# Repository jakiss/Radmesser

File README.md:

# Radmesser
For the enlish version see below.

Das Projekt befasst sich mit der Entwicklung eines Radmessers nach der Idee des Tagesspiegel Berlin (Vgl. https://interaktiv.tagesspiegel.de/radmesser/ und https://github.com/tagesspiegel/radmesser). 

Die genaue des Beschreibung des Projekts mit Grundidee und Annahmen findet sich unter Projektbeschreibung.pdf, um eine kurze Zusammenfassung zu erhalten empfiehlt sich die Datei Zusammenfassung_Projektbeschreibung.pdf.

------------------------------------------------------------
English version:

The project deals with the development of a measurement system for the overtaking distance between cars and bicycles after the idea of the Tagesspeigel Berlin (see https://interaktiv.tagesspiegel.de/radmesser/ and https://github.com/tagesspiegel/radmesser).

The detailed description of the project including the main idea and assumptions  can be found in Projektbeschreibung.pdf. For a short summary of the topic the file Zusammenfassung_Projektbeschreibung.pdf is recommended.

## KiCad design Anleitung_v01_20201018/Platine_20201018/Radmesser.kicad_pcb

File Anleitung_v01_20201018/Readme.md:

Die ausführliche Anleitung finden Sie in der Datei Anleitung.pdf.
Wir haben derzeit noch ein kleines Problem mit unserem Temperatursensor auf der Softwareseite, werden jedoch versuchen dieses so schnell wie möglich zu beheben und ein aktualisiertes Image zur Verfügung zu stellen.

Für den späteren Betrieb ist es wichtig, dass nach einem anfänglichen Blincken im Gleichtakt der LEDs nur noch die grüne LED leuchtet.
Ist dies nicht der Fall, liegt ein Fehler vor. Die rote LED blinkt immer dann auf, wenn ein falscher Messwert aufgezeichent wurde.

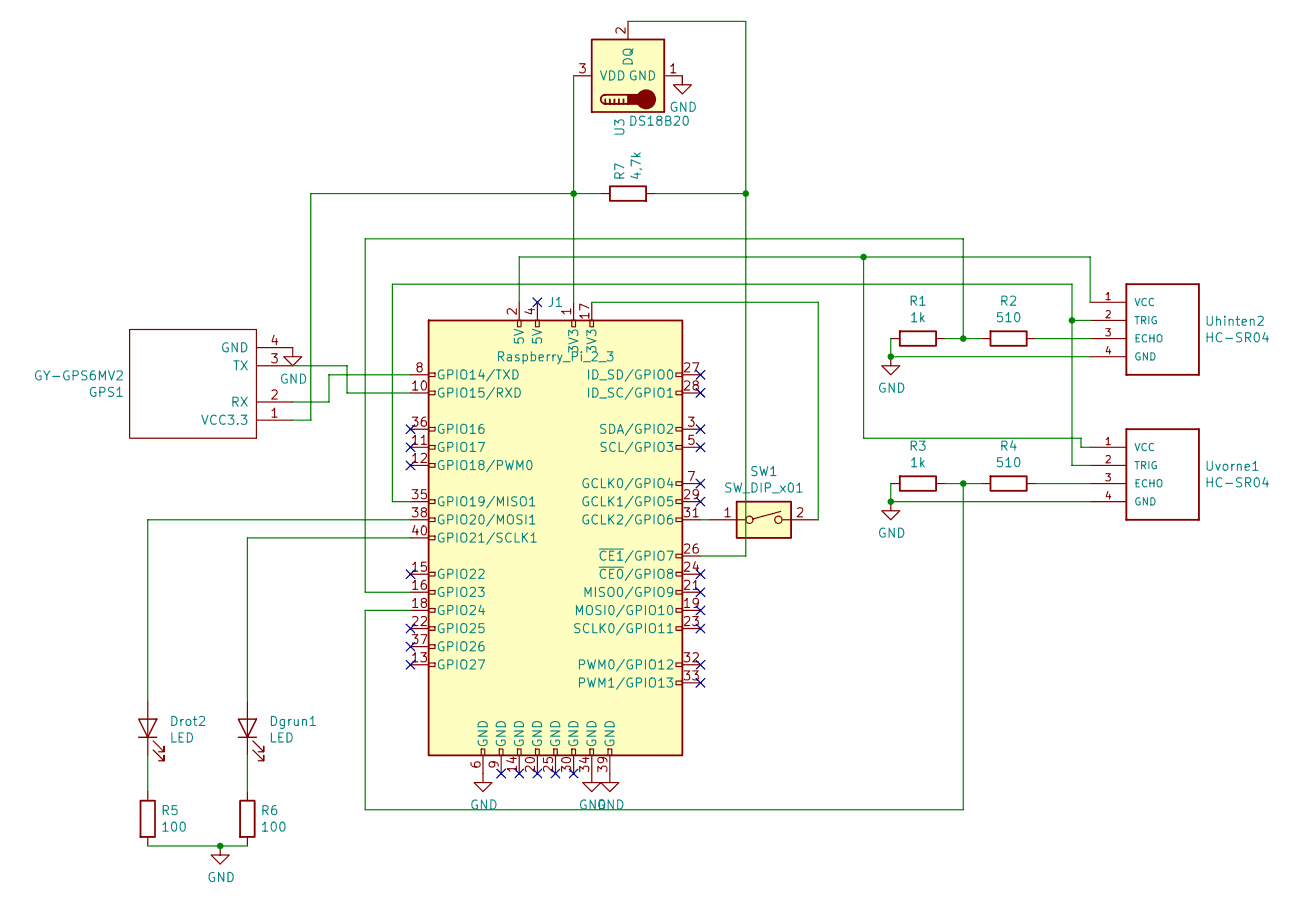
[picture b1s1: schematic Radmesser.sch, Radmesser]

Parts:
Dgrun1: LED; LED_D5.0mm
Drot2: LED; LED_D5.0mm
GPS1: GY-GPS6MV2; GY-GPS6MV
J1: Raspberry_Pi_2_3; PinSocket_2x20_P2.54mm_Vertical
R1, R3: 1k; R_Axial_DIN0207_L6.3mm_D2.5mm_P15.24mm_Horizontal
R2, R4: 510; R_Axial_DIN0207_L6.3mm_D2.5mm_P15.24mm_Horizontal
R5, R6: 100; R_Axial_DIN0207_L6.3mm_D2.5mm_P15.24mm_Horizontal
R7: 4,7k; R_Axial_DIN0207_L6.3mm_D2.5mm_P15.24mm_Horizontal
SW1: SW_DIP_x01; SW_PUSH_6mm_h5mm
U3: DS18B20; TO-220-3_Vertical
Uhinten2: HC-SR04; XCVR_HC-SR04
Uvorne1: HC-SR04; XCVR_HC-SR04

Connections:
GND: GPS1.4 (GND), J1.6 (GND), J1.34 (GND), J1.39 (GND), R1.2, R3.2, R5.2, R6.2, U3.1 (GND), Uhinten2.4 (GND), Uvorne1.4 (GND)
unnamed: Dgrun1.1 (K), R6.1
unnamed: Dgrun1.2 (A), J1.40 (GPIO21/SCLK1)
unnamed: Drot2.1 (K), R5.1
unnamed: Drot2.2 (A), J1.38 (GPIO20/MOSI1)
unnamed: GPS1.1 (VCC3.3), J1.1 (3V3), R7.1, U3.3 (VDD)
unnamed: GPS1.2 (RX), J1.8 (GPIO14/TXD)
unnamed: GPS1.3 (TX), J1.10 (GPIO15/RXD)
unnamed: J1.2 (5V), Uhinten2.1 (VCC), Uvorne1.1 (VCC)
unnamed: J1.16 (GPIO23), R1.1, R2.2
unnamed: J1.17 (3V3), SW1.2
unnamed: J1.18 (GPIO24), R3.1, R4.2
unnamed: J1.26 (~CE1~/GPIO7), R7.2, U3.2 (DQ)
unnamed: J1.31 (GCLK2/GPIO6), SW1.1
unnamed: J1.35 (GPIO19/MISO1), Uhinten2.2 (TRIG), Uvorne1.2 (TRIG)
unnamed: R2.1, Uhinten2.3 (ECHO)
unnamed: R4.1, Uvorne1.3 (ECHO)

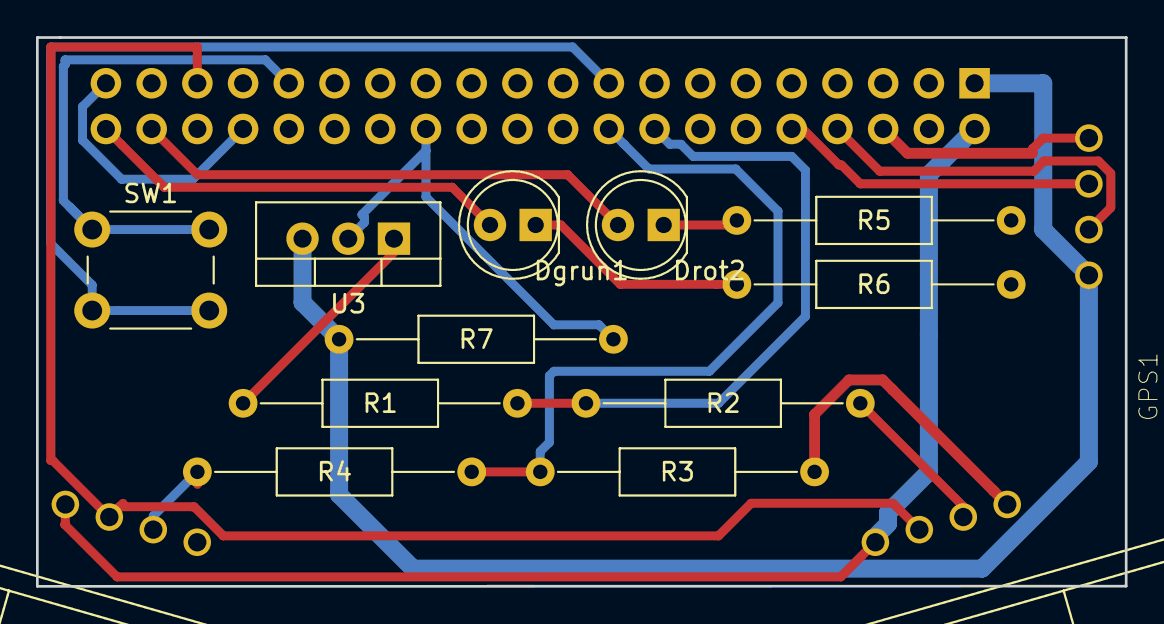
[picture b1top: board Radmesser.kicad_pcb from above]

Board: 2 copper layers, 60.5 x 30.5 mm, 15 parts (1 on the bottom side), 17 nets.

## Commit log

2020-06-14 Short overview of the topic
    This file shows the main points of the realized project. It was written at the Baden-Wuerttemberg Cooperative State University from October 2019 to June 2020.
2020-06-14 Detailed information about the project
    This file gives detailed information about the realized project, including source code from June 2020.
2020-06-14 Script for the Raspberry Pi Zero
2020-06-14 Convert GPS of overtakes into adress
2020-06-14 Update GPS_to_Adress_over_API.R
    Source code needs the library from https://github.com/juliusgh/opencage to get the detailed road info that ist wanted for the evaluation of the overtakings.
2020-08-08 new_data
2020-08-20 Ergebnisse Testfahrt 2020-08-16
2020-09-05 file name changed
2020-09-08 added new evaluation
2020-10-05 added evaluation software
2020-10-18 Anleitung added for interests
2020-10-19 leichte Verbesserungen
2020-11-05 Kommentierter Quellcode und unnötiges entfernt
